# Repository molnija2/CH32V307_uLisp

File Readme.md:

This project is "Arduino-free" C++ version of the uLisp-4.7 interpreter for microcontrollers developed by David Johnson-Davies (http://www.ulisp.com/)

The project is developed espessialy for CH32V307VCT or CH32V30x microcontrollers.

The project can be compiled by MounRiver Studio. It is nessessary to tune this project options for C++ instide of C ( manual is here https://github.com/openwch/ch32v307/tree/main/C%2B%2B).
A template project from MounRiver Studio was used in the developement. 

This version supports sdcard commands.

An external SRAM memory support is included same.

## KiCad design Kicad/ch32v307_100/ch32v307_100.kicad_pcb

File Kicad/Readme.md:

Kicad schematic project of the unit.
CH32V307VCT6 + external SRAM, SDCard, extention connectors for LCD(TFT) and other peripherals.

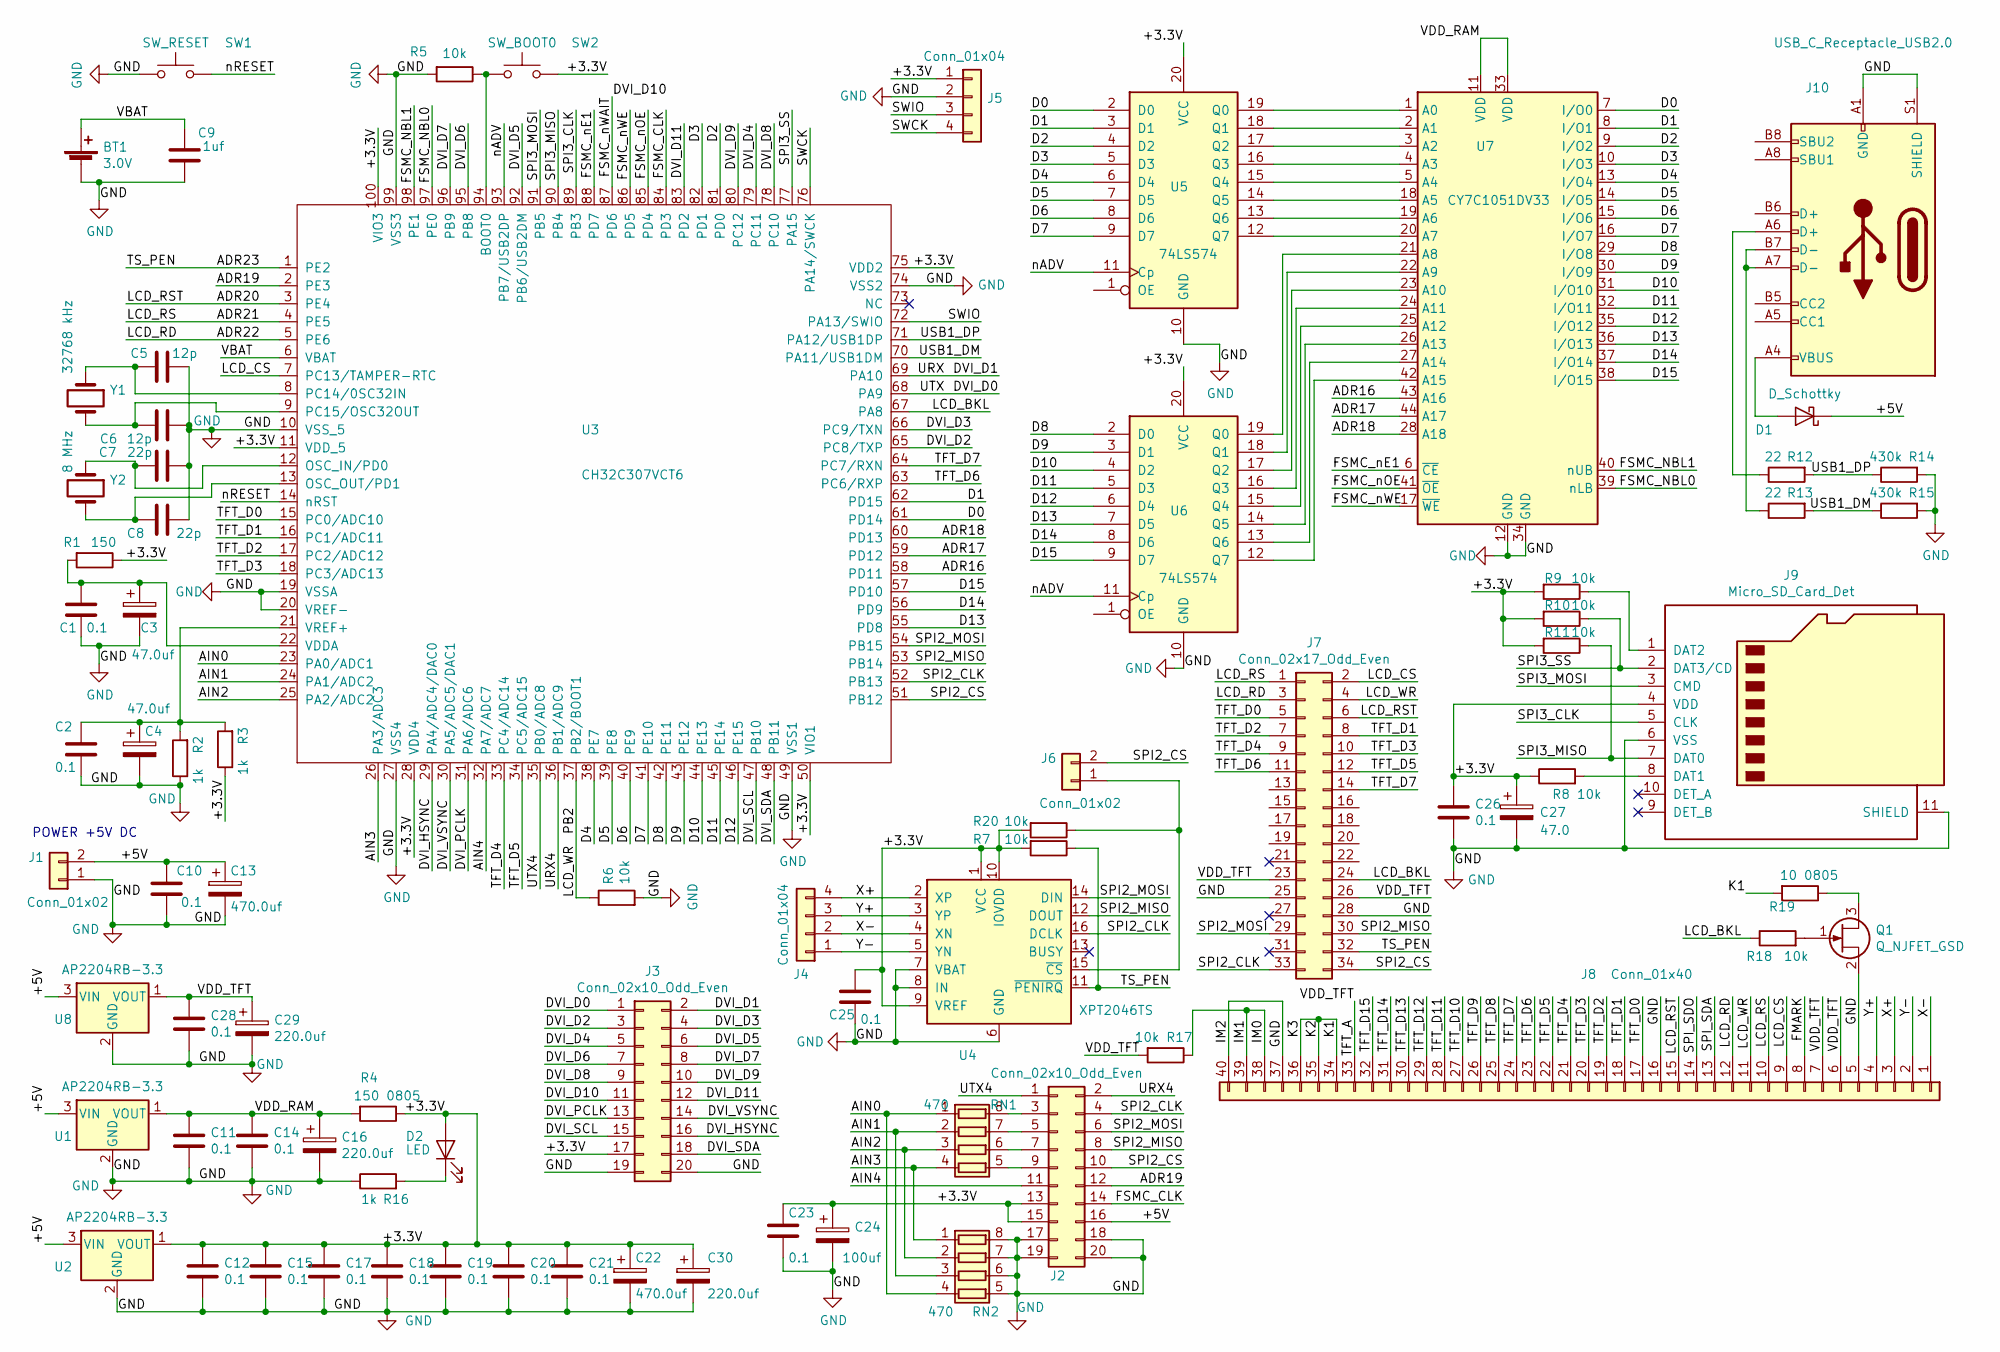
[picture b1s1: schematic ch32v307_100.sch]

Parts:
BT1: 3.0V; Battery_CR1225_SMD
C1, C2: 0.1; R_0603_1608Metric
C3, C4: 47.0uf; CP_Elec_4x5.4
C5, C6: 12p; C_0603_1608Metric
C7, C8: 22p; C_0603_1608Metric
C9: 1uf; C_0805_2012Metric
C10, C11, C12, C14, C15, C17, C18, C19, C20, C21, C23, C25, C26, C28: 0.1; C_0603_1608Metric
C13, C22: 470.0uf; CP_Radial_D6.3mm_P2.50mm
C16, C29, C30: 220.0uf; CP_Elec_6.3x5.4
C24: 100uf; CP_Elec_5x5.4
C27: 47.0; CP_Elec_4x5.4
D1: D_Schottky; D_1210_3225Metric
D2: LED; LED_0805_2012Metric
J1, J6: Conn_01x02; PinHeader_1x02_P2.54mm_Vertical
J2, J3: Conn_02x10_Odd_Even; PinHeader_2x10_P2.54mm_Vertical
J4, J5: Conn_01x04; PinHeader_1x04_P2.54mm_Vertical
J7: Conn_02x17_Odd_Even; PinHeader_2x17_P2.54mm_Vertical
J8: Conn_01x40; Hirose_FH12-40S-0.5SH_1x40-1MP_P0.50mm_Horizontal
J9: Micro_SD_Card_Det; microSD__my_footprint
J10: USB_C_Receptacle_USB2.0; USB_C_Receptacle_Palconn_UTC16-G
Q1: Q_NJFET_GSD; SC-59_Handsoldering
R1: 150; R_0603_1608Metric
R2, R3, R16: 1k; R_0603_1608Metric
R4: 150 0805; R_0805_2012Metric
R5, R6, R7, R8, R9, R10, R11, R17, R18, R20: 10k; R_0603_1608Metric
R12, R13: 22; R_0603_1608Metric
R14, R15: 430k; R_0603_1608Metric
R19: 10 0805; R_0805_2012Metric
RN1, RN2: 470; R_Array_Convex_4x0612
SW1: SW_RESET; SW_PUSH_6.0x3.2mm
SW2: SW_BOOT0; SW_PUSH_6.0x3.2mm
U1, U2, U8: AP2204RB-3.3; SOT-89-3
U3: CH32C307VCT6; LQFP-100_14x14mm_P0.5mm
U4: XPT2046TS; TSSOP-16_4.4x5mm_P0.65mm
U5, U6: 74LS574; SSOP-20_4.4x6.5mm_P0.65mm
U7: CY7C1051DV33; TSOP-II-44_10.16x18.41mm_P0.8mm
Y1: 32768 kHz; Crystal_SMD_3215-2Pin_3.2x1.5mm
Y2: 8 MHz; Crystal_SMD_3225-4Pin_3.2x2.5mm_HandSoldering

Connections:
/+3.3V: C12.2, C15.2, C17.2, C18.2, C19.2, C20.2, C21.2, C22.1, C23.2, C24.1, C25.2, C26.2, C27.1, C30.1, D2.2 (A), J2.13, J2.15, J3.17, J5.1, J9.4 (VDD), R1.1, R3.1, R4.1, R7.2, R8.1, R9.2, R10.2, R11.2, R20.2, SW2.2, U2.1 (VOUT), U3.11 (VDD_5), U3.28 (VDD4), U3.50 (VIO1), U3.75 (VDD2), U3.100 (VIO3), U4.1 (VCC), U4.9 (VREF), U4.10 (IOVDD), U5.20 (VCC), U6.20 (VCC)
/+5V: C10.2, C13.1, D1.1 (K), J1.2, J2.16, U1.3 (VIN), U2.3 (VIN), U8.3 (VIN)
/ADR16: U3.58 (PD11), U7.43 (A16)
/ADR17: U3.59 (PD12), U7.44 (A17)
/ADR18: U3.60 (PD13), U7.28 (A18)
/ADR19: J2.12, U3.2 (PE3)
/ADR20: J7.6, J8.15, U3.3 (PE4)
/ADR21: J7.1, J8.10, U3.4 (PE5)
/ADR22: J7.3, J8.12, U3.5 (PE6)
/ADR23: J7.32, R7.1, U3.1 (PE2), U4.11 (~PENIRQ)
/AIN0: RN1.1 (R1.1), RN2.4 (R4.1), U3.23 (PA0/ADC1)
/AIN1: RN1.2 (R2.1), RN2.3 (R3.1), U3.24 (PA1/ADC2)
/AIN2: RN1.3 (R3.1), RN2.2 (R2.1), U3.25 (PA2/ADC2)
/AIN3: RN1.4 (R4.1), RN2.1 (R1.1), U3.26 (PA3/ADC3)
/AIN4: J2.11, U3.32 (PA7/ADC7)
/D0: U3.61 (PD14), U5.2 (D0), U7.7 (I/O0)
/D1: U3.62 (PD15), U5.3 (D1), U7.8 (I/O1)
/D2: U3.81 (PD0), U5.4 (D2), U7.9 (I/O2)
/D3: U3.82 (PD1), U5.5 (D3), U7.10 (I/O3)
/D4: U3.38 (PE7), U5.6 (D4), U7.13 (I/O4)
/D5: U3.39 (PE8), U5.7 (D5), U7.14 (I/O5)
/D6: U3.40 (PE9), U5.8 (D6), U7.15 (I/O6)
/D7: U3.41 (PE10), U5.9 (D7), U7.16 (I/O7)
/D8: U3.42 (PE11), U6.2 (D0), U7.29 (I/O8)
/D9: U3.43 (PE12), U6.3 (D1), U7.30 (I/O9)
/D10: U3.44 (PE13), U6.4 (D2), U7.31 (I/O10)
/D11: U3.45 (PE14), U6.5 (D3), U7.32 (I/O11)
/D12: U3.46 (PE15), U6.6 (D4), U7.35 (I/O12)
/D13: U3.55 (PD8), U6.7 (D5), U7.36 (I/O13)
/D14: U3.56 (PD9), U6.8 (D6), U7.37 (I/O14)
/D15: U3.57 (PD10), U6.9 (D7), U7.38 (I/O15)
/DVI_D0: J3.1, U3.68 (PA9)
/DVI_D1: J3.2, U3.69 (PA10)
/DVI_D2: J3.3, U3.65 (PC8/TXP)
/DVI_D3: J3.4, U3.66 (PC9/TXN)
/DVI_D4: J3.5, U3.79 (PC11)
/DVI_D5: J3.6, U3.92 (PB6/USB2DM)
/DVI_D6: J3.7, U3.95 (PB8)
/DVI_D7: J3.8, U3.96 (PB9)
/DVI_D8: J3.9, U3.78 (PC10)
/DVI_D9: J3.10, U3.80 (PC12)
/DVI_D10: J3.11, U3.87 (PD6)
/DVI_D11: J3.12, U3.83 (PD2)
/DVI_HSYNC: J3.16, U3.29 (PA4/ADC4/DAC0)
/DVI_PCLK: J3.13, U3.31 (PA6/ADC6)
/DVI_SCL: J3.15, U3.47 (PB10)
/DVI_SDA: J3.18, U3.48 (PB11)
/DVI_VSYNC: J3.14, U3.30 (PA5/ADC5/DAC1)
/FMARK: J8.8
/FSMC_CLK: J2.14, U3.84 (PD3)
/FSMC_NBL0: U3.97 (PE0), U7.39 (nLB)
/FSMC_NBL1: U3.98 (PE1), U7.40 (nUB)
/FSMC_nE1: U3.88 (PD7), U7.6 (~CE)
/FSMC_nOE: U3.85 (PD4), U7.41 (~OE)
/FSMC_nWE: U3.86 (PD5), U7.17 (~WE)
/IM0: J8.38, J8.39, R17.1
/K1: J8.34, J8.35, J8.36, R19.2
/LCD_BKL: J7.24, R18.1, U3.67 (PA8)
/LCD_CS: J7.2, J8.9, U3.7 (PC13/TAMPER-RTC)
/LCD_WR: J7.4, J8.11, R6.1, U3.37 (PB2/BOOT1)
/SPI2_CLK: J2.4, J7.33, U3.52 (PB13), U4.16 (DCLK)
/SPI2_CS: J2.10, J6.2, J7.34, U3.51 (PB12)
/SPI2_MISO: J2.8, J7.30, U3.53 (PB14), U4.12 (DOUT)
/SPI2_MOSI: J2.6, J7.29, U3.54 (PB15), U4.14 (DIN)
/SPI3_CLK: J9.5 (CLK), U3.89 (PB3)
/SPI3_MISO: J9.7 (DAT0), R11.1, U3.90 (PB4)
/SPI3_MOSI: J9.3 (CMD), U3.91 (PB5)
/SPI3_SS: J9.2 (DAT3/CD), R10.1, U3.77 (PA15)
/SPI_SDA: J8.13
/SPI_SDO: J8.14
/SWCK: J5.4, U3.76 (PA14/SWCK)
/SWIO: J5.3, U3.72 (PA13/SWIO)
/TFT_A: C28.2, C29.1, J7.23, J7.26, J8.6, J8.7, J8.33, R17.2, U8.1 (VOUT)
/TFT_D0: J7.5, J8.17, U3.15 (PC0/ADC10)
/TFT_D1: J7.8, J8.18, U3.16 (PC1/ADC11)
/TFT_D2: J7.7, J8.19, U3.17 (PC2/ADC12)
/TFT_D3: J7.10, J8.20, U3.18 (PC3/ADC13)
/TFT_D4: J7.9, J8.21, U3.33 (PC4/ADC14)
/TFT_D5: J7.12, J8.22, U3.34 (PC5/ADC15)
/TFT_D6: J7.11, J8.23, U3.63 (PC6/RXP)
/TFT_D7: J7.14, J8.24, U3.64 (PC7/RXN)
/TFT_D8: J8.25
/TFT_D9: J8.26
/TFT_D10: J8.27
/TFT_D11: J8.28
/TFT_D12: J8.29
/TFT_D13: J8.30
/TFT_D14: J8.31
/TFT_D15: J8.32
/URX4: J2.2, U3.36 (PB1/ADC9)
/USB1_DM: R13.2, R15.1, U3.70 (PA11/USB1DM)
/USB1_DP: R12.2, R14.1, U3.71 (PA12/USB1DP)
/UTX4: J2.1, U3.35 (PB0/ADC8)
/VBAT: BT1.1 (+), C9.1, U3.6 (VBAT)
/VDD_RAM: C11.2, C14.2, C16.1, R4.2, U1.1 (VOUT), U7.11 (VDD), U7.33 (VDD)
/X+: J4.4, J8.3, U4.2 (XP)
/X-: J4.2, J8.1, U4.4 (XN)
/Y+: J4.3, J8.4, U4.3 (YP)
/Y-: J4.1, J8.2, U4.5 (YN)
/nADV: U3.93 (PB7/USB2DP), U5.11 (Cp), U6.11 (Cp)
/nRESET: SW1.2, U3.14 (nRST)
GND: BT1.2 (-), C1.1, C2.1, C3.2, C4.2, C5.1, C6.2, C7.1, C8.2, C9.2, C10.1, C11.1, C12.1, C13.2, C14.1, C15.1, C16.2, C17.1, C18.1, C19.1, C20.1, C21.1, C22.2, C23.1, C24.2, C25.1, C26.1, C27.2, C28.1, C29.2, C30.2, J1.1, J2.17, J2.18, J2.19, J2.20, J3.19, J3.20, J5.2, J7.25, J7.28, J8.5, J8.16, J8.37, J8.40, J9.6 (VSS), J9.11 (SHIELD), J10.A1 (GND), J10.A12 (GND), J10.B1 (GND), J10.B12 (GND), J10.S1 (SHIELD), Q1.2 (S), R2.1, R5.2, R6.2, R14.2, R15.2, R16.1, RN2.5 (R4.2), RN2.6 (R3.2), RN2.7 (R2.2), RN2.8 (R1.2), SW1.1, U1.2 (GND), U2.2 (GND), U3.10 (VSS_5), U3.19 (VSSA), U3.20 (VREF-), U3.27 (VSS4), U3.49 (VSS1), U3.74 (VSS2), U3.99 (VSS3), U4.6 (GND), U4.7 (VBAT), U4.8 (IN), U5.10 (GND), U6.10 (GND), U7.12 (GND), U7.34 (GND), U8.2 (GND)
unnamed: C1.2, C3.1, R1.2, U3.22 (VDDA)
unnamed: C2.2, C4.1, R2.2, R3.2, U3.21 (VREF+)
unnamed: C5.2, U3.8 (PC14/0SC32IN), Y1.1
unnamed: C6.1, U3.9 (PC15/OSC32OUT), Y1.2
unnamed: C7.2, U3.12 (OSC_IN/PD0), Y2.1
unnamed: C8.1, U3.13 (OSC_OUT/PD1), Y2.2
unnamed: D1.2 (A), J10.A4 (VBUS), J10.A9 (VBUS), J10.B4 (VBUS), J10.B9 (VBUS)
unnamed: D2.1 (K), R16.2
unnamed: J2.3, RN1.8 (R1.2)
unnamed: J2.5, RN1.7 (R2.2)
unnamed: J2.7, RN1.6 (R3.2)
unnamed: J2.9, RN1.5 (R4.2)
unnamed: J6.1, R20.1, U4.15 (~CS)
unnamed: J9.1 (DAT2), R9.1
unnamed: J9.8 (DAT1), R8.2
unnamed: J10.A6 (D+), R12.1
unnamed: J10.A7 (D-), J10.B7 (D-), R13.1
unnamed: Q1.1 (G), R18.2
unnamed: Q1.3 (D), R19.1
unnamed: R5.1, SW2.1, U3.94 (BOOT0)
unnamed: U5.12 (Q7), U7.20 (A7)
unnamed: U5.13 (Q6), U7.19 (A6)
unnamed: U5.14 (Q5), U7.18 (A5)
unnamed: U5.15 (Q4), U7.5 (A4)
unnamed: U5.16 (Q3), U7.4 (A3)
unnamed: U5.17 (Q2), U7.3 (A2)
unnamed: U5.18 (Q1), U7.2 (A1)
unnamed: U5.19 (Q0), U7.1 (A0)
unnamed: U6.12 (Q7), U7.42 (A15)
unnamed: U6.13 (Q6), U7.27 (A14)
unnamed: U6.14 (Q5), U7.26 (A13)
unnamed: U6.15 (Q4), U7.25 (A12)
unnamed: U6.16 (Q3), U7.24 (A11)
unnamed: U6.17 (Q2), U7.23 (A10)
unnamed: U6.18 (Q1), U7.22 (A9)
unnamed: U6.19 (Q0), U7.21 (A8)

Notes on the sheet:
POWER +5V DC

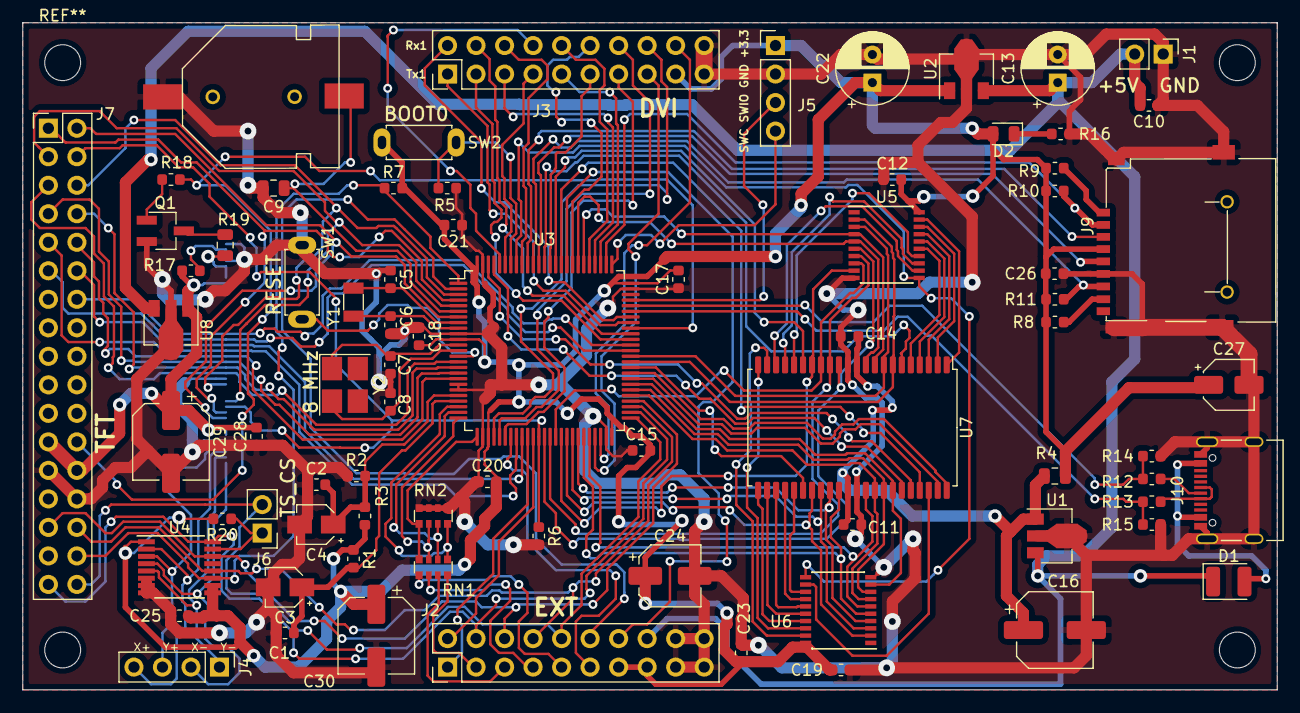
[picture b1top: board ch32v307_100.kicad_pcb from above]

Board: 2 copper layers, 111.8 x 59.4 mm, 78 parts (1 on the bottom side), 127 nets.
